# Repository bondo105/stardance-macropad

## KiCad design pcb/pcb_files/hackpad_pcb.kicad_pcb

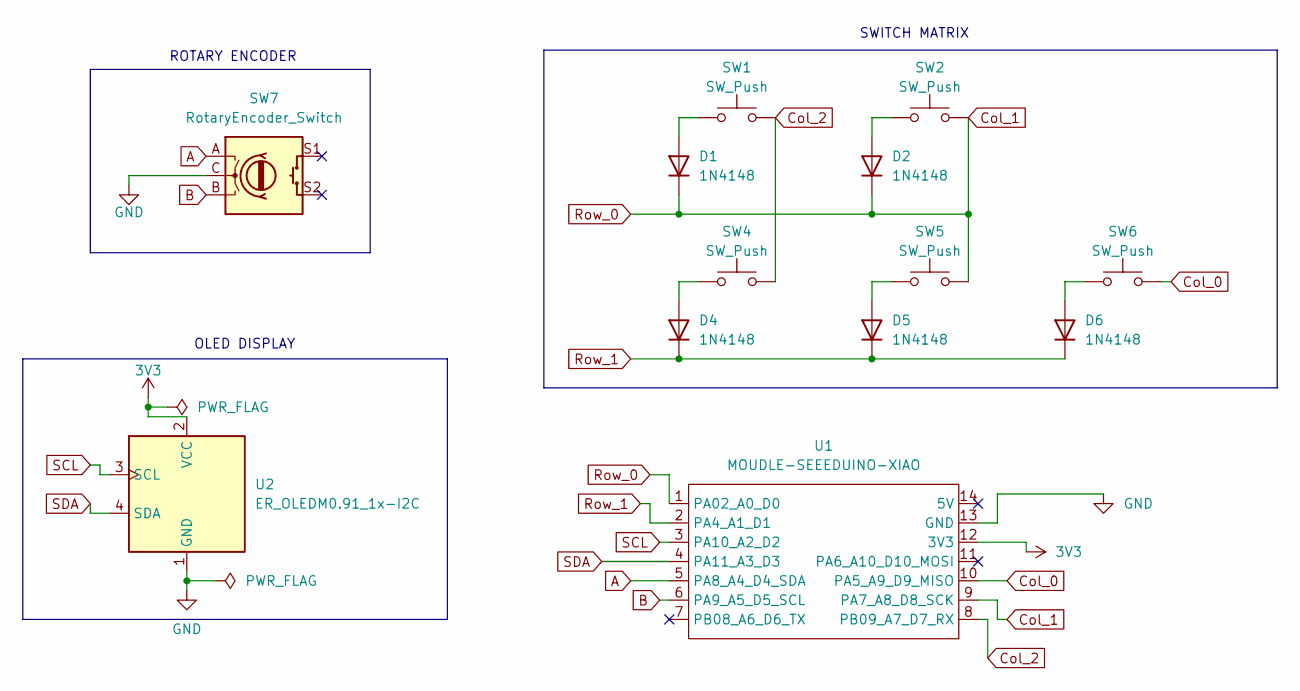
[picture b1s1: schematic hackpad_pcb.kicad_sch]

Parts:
D1, D2, D4, D5, D6: 1N4148; D_DO-35_SOD27_P7.62mm_Horizontal
SW1, SW2, SW4, SW5, SW6: SW_Push; SW_Cherry_MX_1.00u_PCB
SW7: RotaryEncoder_Switch; RotaryEncoder_Alps_EC11E-Switch_Vertical_H20mm
U1: MOUDLE-SEEEDUINO-XIAO; XIAO-Generic-Hybrid-14P-2.54-21X17.8MM
U2: ER_OLEDM0.91_1x-I2C

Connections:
3V3: U1.12 (3V3), U2.2 (VCC)
A: SW7.A, U1.5 (PA8_A4_D4_SDA)
B: SW7.B, U1.6 (PA9_A5_D5_SCL)
Col_0: SW6.2, U1.10 (PA5_A9_D9_MISO)
Col_1: D1.1 (K), D2.1 (K), SW2.2, SW5.2, U1.1 (PA02_A0_D0), U1.9 (PA7_A8_D8_SCK)
Col_2: SW1.2, SW4.2, U1.8 (PB09_A7_D7_RX)
GND: SW7.C, U1.13 (GND), U2.1 (GND)
unnamed: D1.2 (A), SW1.1
unnamed: D2.2 (A), SW2.1
unnamed: D4.2 (A), SW4.1
unnamed: D5.2 (A), SW5.1
unnamed: D6.2 (A), SW6.1
Row_1: D4.1 (K), D5.1 (K), D6.1 (K), U1.2 (PA4_A1_D1)
SCL: U1.3 (PA10_A2_D2), U2.3 (SCL)
SDA: U1.4 (PA11_A3_D3), U2.4 (SDA)

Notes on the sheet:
SWITCH MATRIX
OLED DISPLAY
ROTARY ENCODER

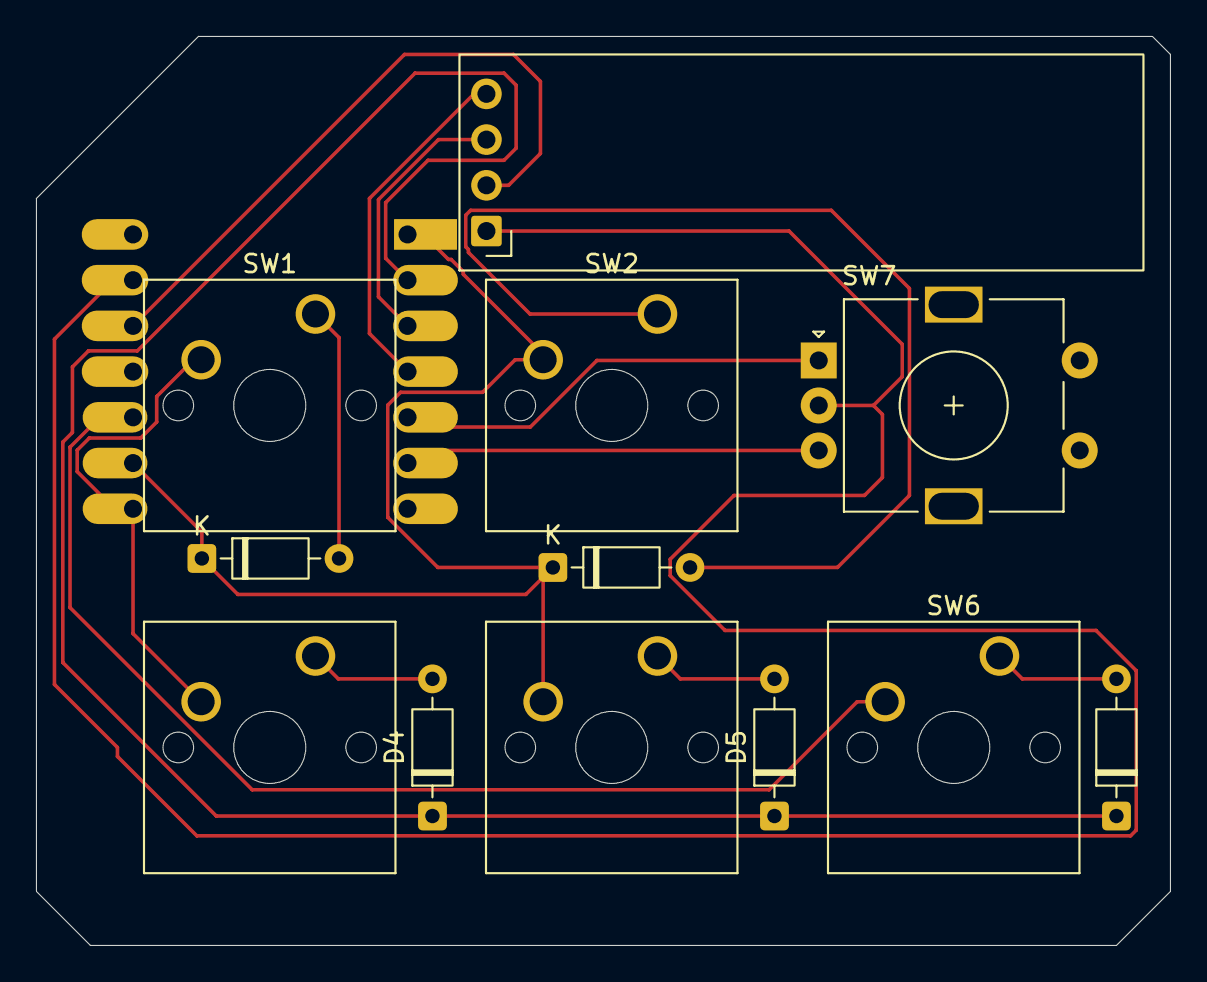
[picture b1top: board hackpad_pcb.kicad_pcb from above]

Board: 2 copper layers, 63.0 x 50.5 mm, 13 parts (1 on the bottom side), 15 nets.

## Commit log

2026-06-11 KiCad folder setup
2026-06-11 Modified Schematic
2026-06-11 Finished the schematic
2026-06-12 Completed the PCB
2026-06-12 Removed redundant files
2026-06-13 Updated the PCB
2026-06-13 Small changes to PCB
